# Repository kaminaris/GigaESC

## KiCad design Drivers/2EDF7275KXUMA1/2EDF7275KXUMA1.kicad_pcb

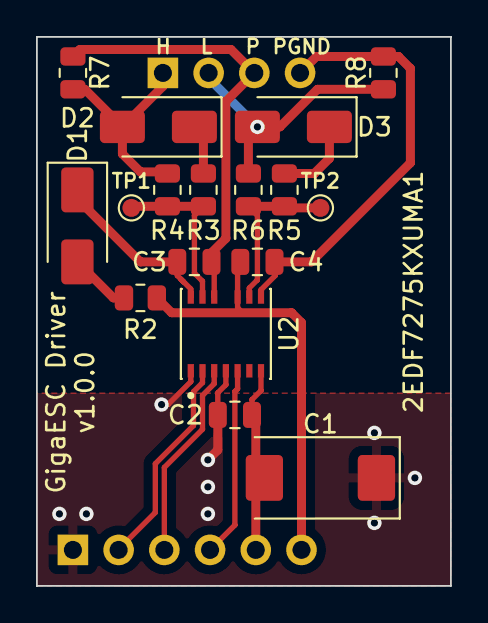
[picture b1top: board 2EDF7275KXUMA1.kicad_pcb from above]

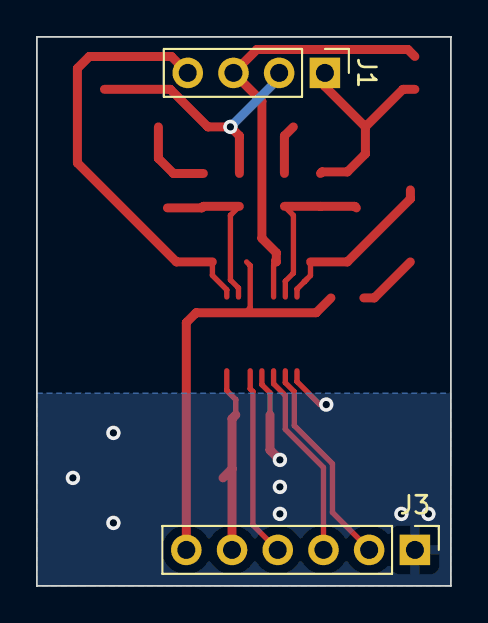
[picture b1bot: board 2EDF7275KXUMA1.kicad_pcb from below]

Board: 2 copper layers, 23.0 x 30.5 mm, 19 parts (2 on the bottom side), 16 nets.

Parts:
C1: 47u 25v Tant; CP_EIA-7343-31_Kemet-D
C2: 100n; C_0805_2012Metric
C3, C4: 4.7u 25v; C_0805_2012Metric
D1, D2, D3: SS520F; D_SMA
J1: Output; PinHeader_1x04_P2.54mm_Vertical
J3: Input; PinHeader_1x06_P2.54mm_Vertical
R2, R3, R4, R5, R6: 2.2; R_0805_2012Metric
R7, R8: 4.7k; R_0805_2012Metric
TP1, TP2: TestPoint; TestPoint_Pad_D1.0mm
U2: 2EDF7275KXUMA1; IC_2EDF7275KXUMA2

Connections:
+3.3V: C1.2, C2.1, J3.5, U2.7 (VDDI)
+15V: C4.1, J3.6, R2.1, U2.10 (VDDB)
/DISABLE: J3.4, U2.5 (DISABLE)
/H: J3.2, U2.2 (INA)
/L: J3.3, U2.3 (INB)
/PH: D2.2 (A), J1.1, R4.2, R7.2
/PHASE: C3.2, J1.3, R7.1, U2.11 (GNDA)
/PHASE_GROUND: C4.2, J1.4, R8.1, U2.8 (GNDB)
/PL: D3.2 (A), J1.2, R6.2, R8.2
GND: C1.1, C2.2, J3.1, U2.1 (GNDI), U2.4 (SLDON)
unnamed: D1.2 (A), R2.2
unnamed: C3.1, D1.1 (K), U2.13 (VDDA)
unnamed: D2.1 (K), R3.2
unnamed: D3.1 (K), R5.2
unnamed: R3.1, R4.1, TP1.1, U2.12 (OUTA)
unnamed: R5.1, R6.1, TP2.1, U2.9 (OUTB)

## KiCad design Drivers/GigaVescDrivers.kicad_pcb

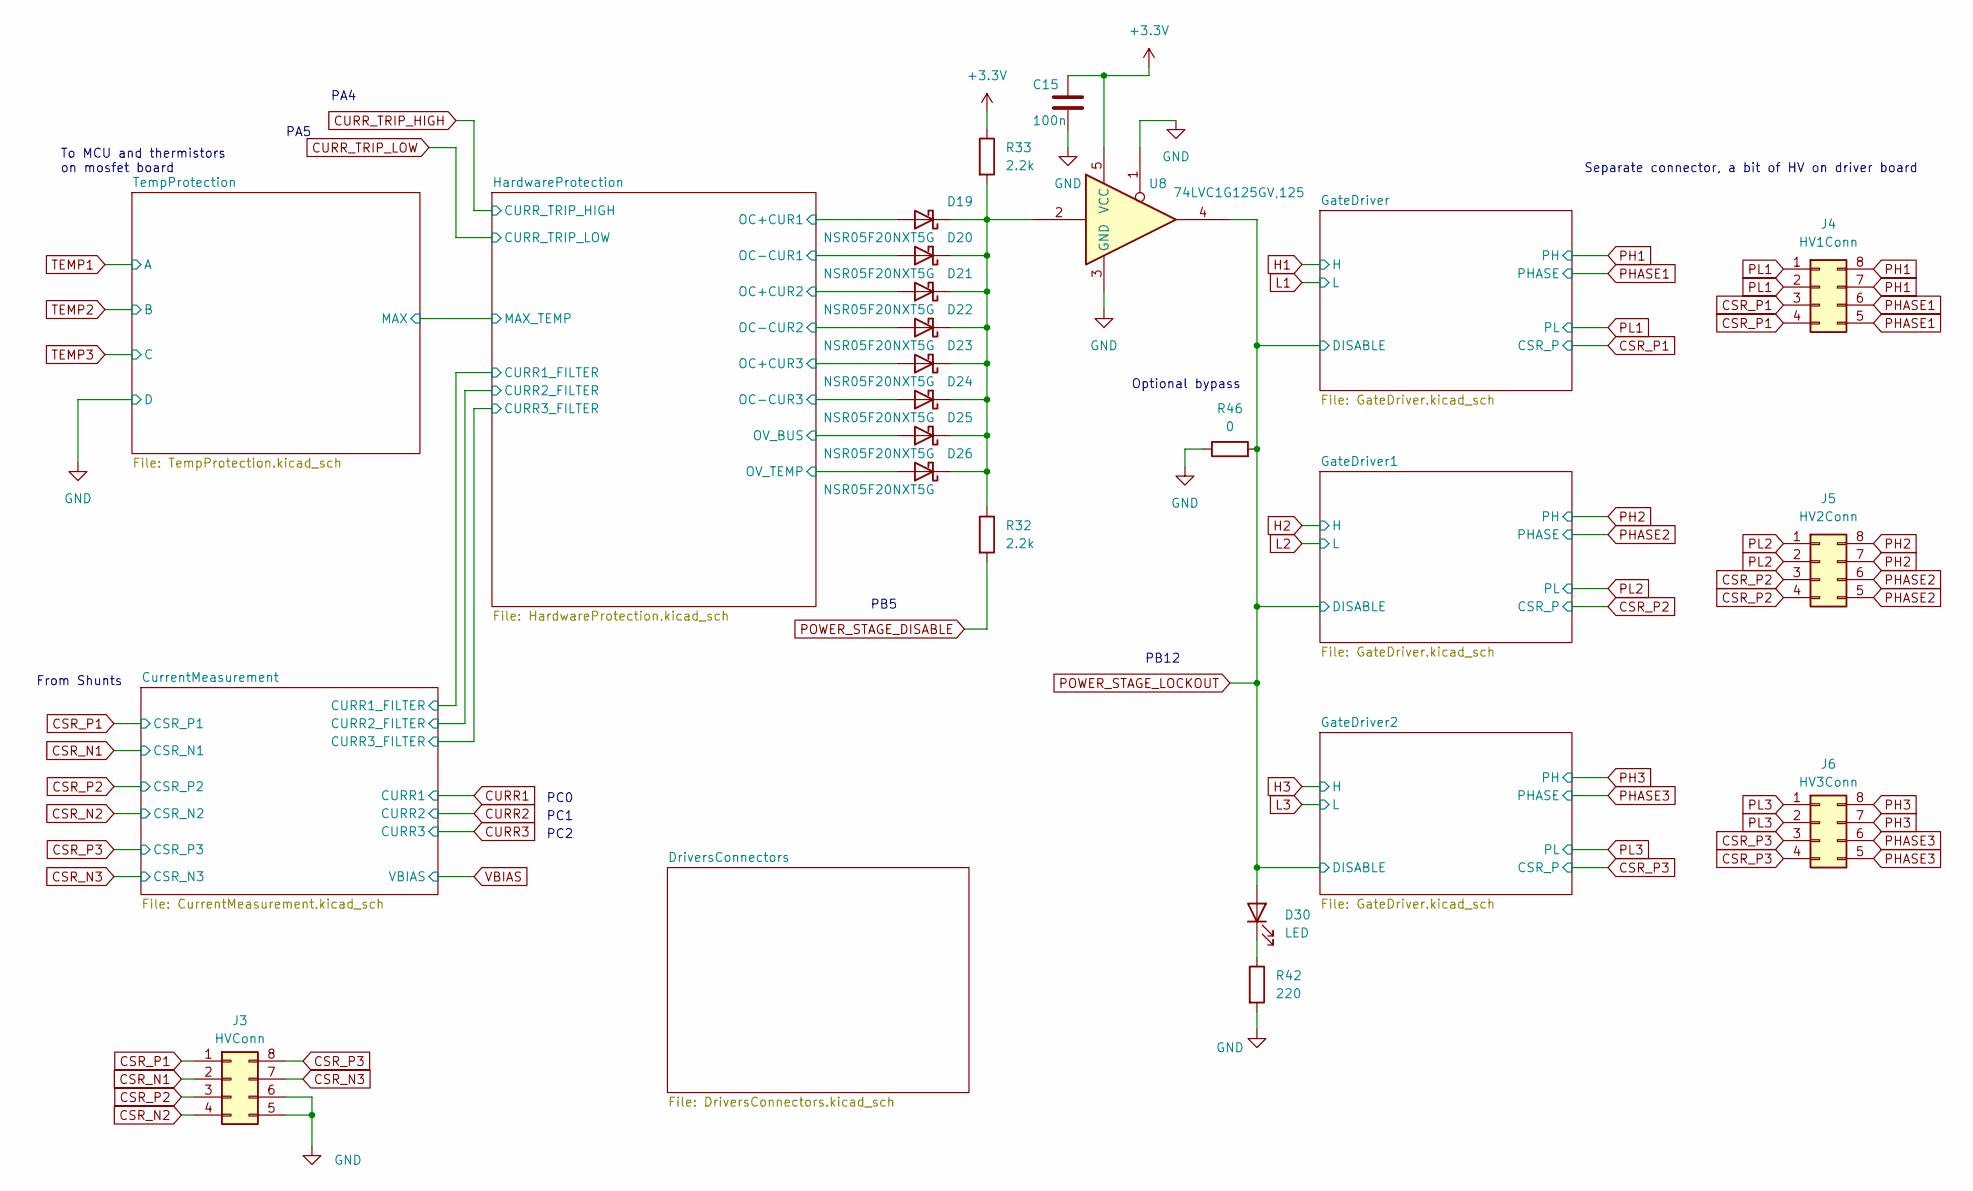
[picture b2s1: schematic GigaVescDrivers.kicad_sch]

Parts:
C15: 100n; C_0805_2012Metric
D19, D20, D21, D22, D23, D24, D25, D26: NSR05F20NXT5G; D_0402_1005Metric
D30: LED; LED_0805_2012Metric
J3: HVConn; PinHeader_2x04_P2.54mm_Vertical
J4: HV1Conn; PinHeader_2x04_P2.54mm_Vertical
J5: HV2Conn; PinHeader_2x04_P2.54mm_Vertical
J6: HV3Conn; PinHeader_2x04_P2.54mm_Vertical
R32, R33: 2.2k; R_0805_2012Metric
R42: 220; R_0805_2012Metric
R46: 0; R_0805_2012Metric
U8: 74LVC1G125GV,125; TSOP-5_1.65x3.05mm_P0.95mm

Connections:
+3.3V: C15.1, R33.1, U8.5 (VCC); also elsewhere on the board
/HardwareProtection/OC+CUR1: D19.2 (A); also elsewhere on the board
/HardwareProtection/OC+CUR2: D21.2 (A); also elsewhere on the board
/HardwareProtection/OC+CUR3: D23.2 (A); also elsewhere on the board
/HardwareProtection/OC-CUR1: D20.2 (A); also elsewhere on the board
/HardwareProtection/OC-CUR2: D22.2 (A); also elsewhere on the board
/HardwareProtection/OC-CUR3: D24.2 (A); also elsewhere on the board
/HardwareProtection/OV_BUS: D25.2 (A); also elsewhere on the board
/HardwareProtection/OV_TEMP: D26.2 (A); also elsewhere on the board
CSR_N1: J3.2; also elsewhere on the board
CSR_N2: J3.4; also elsewhere on the board
CSR_N3: J3.7; also elsewhere on the board
CSR_P1: J3.1, J4.3, J4.4; also elsewhere on the board
CSR_P2: J3.3, J5.3, J5.4; also elsewhere on the board
CSR_P3: J3.8, J6.3, J6.4; also elsewhere on the board
GND: C15.2, J3.5, J3.6, R42.2, R46.1, U8.1, U8.3 (GND); also elsewhere on the board
unnamed: D19.1 (K), D20.1 (K), D21.1 (K), D22.1 (K), D23.1 (K), D24.1 (K), D25.1 (K), D26.1 (K), R32.1, R33.2, U8.2
unnamed: D30.1 (K), R42.1
PH1: J4.7, J4.8; also elsewhere on the board
PH2: J5.7, J5.8; also elsewhere on the board
PH3: J6.7, J6.8; also elsewhere on the board
PHASE1: J4.5, J4.6; also elsewhere on the board
PHASE2: J5.5, J5.6; also elsewhere on the board
PHASE3: J6.5, J6.6; also elsewhere on the board
PL1: J4.1, J4.2; also elsewhere on the board
PL2: J5.1, J5.2; also elsewhere on the board
PL3: J6.1, J6.2; also elsewhere on the board
POWER_STAGE_DISABLE: R32.2; also elsewhere on the board
POWER_STAGE_LOCKOUT: D30.2 (A), R46.2, U8.4; also elsewhere on the board

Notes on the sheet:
PA5
PA4
PC2
PB12
Optional bypass
PB5
Separate connector, a bit of HV on driver board
To MCU and thermistors on mosfet board
PC1
PC0
From Shunts

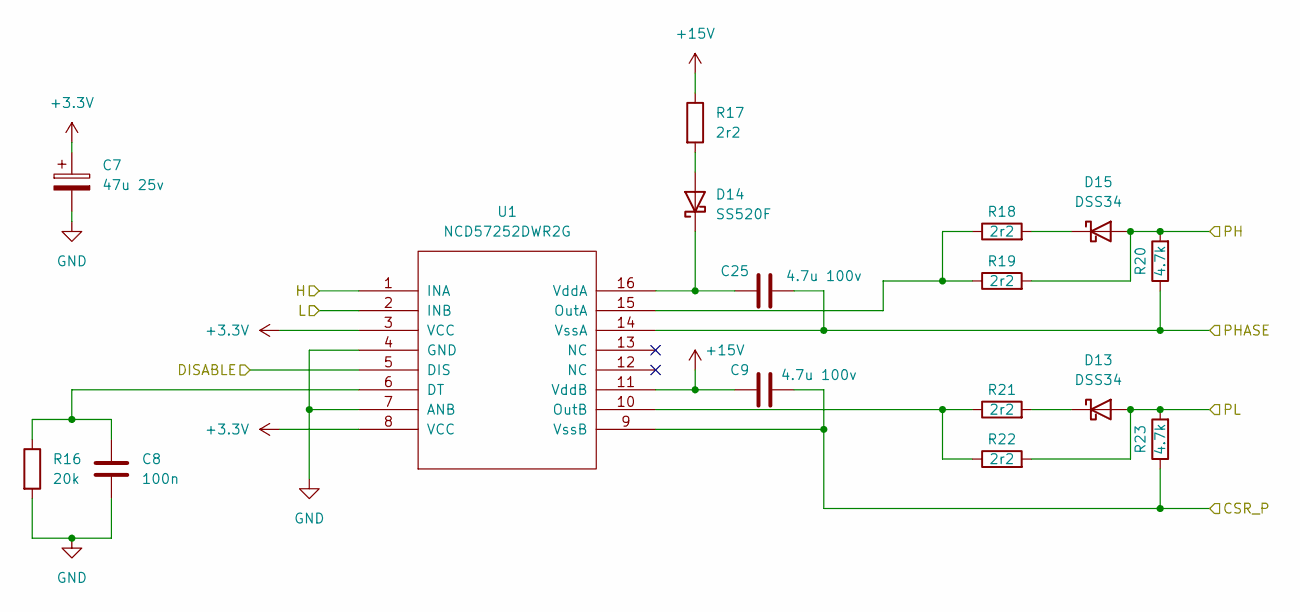
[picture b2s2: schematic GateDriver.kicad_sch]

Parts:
C7: 47u 25v; CP_Elec_5x5.4
C8: 100n; C_0805_2012Metric
C9, C25: 4.7u 100v; C_0805_2012Metric
D13, D15: DSS34; D_SOD-123F
D14: SS520F; D_SMA
R16: 20k; R_0805_2012Metric
R17, R18, R19, R21, R22: 2r2; R_0805_2012Metric
R20, R23: 4.7k; R_0805_2012Metric
U1: NCD57252DWR2G; SOIC-16W_7.5x10.3mm_P1.27mm

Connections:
+3.3V: C7.1, U1.3 (VCC), U1.8 (VCC); also elsewhere on the board
+15V: C9.1, R17.1, U1.11 (VddB); also elsewhere on the board
CSR_P1: C9.2, R23.1, U1.9 (VssB); also elsewhere on the board
GND: C7.2, C8.2, R16.2, U1.4 (GND), U1.7 (ANB); also elsewhere on the board
H1: U1.1 (INA); also elsewhere on the board
L1: U1.2 (INB); also elsewhere on the board
unnamed: D13.1 (K), R21.2
unnamed: D14.2 (A), R17.2
unnamed: C25.1, D14.1 (K), U1.16 (VddA)
unnamed: D15.1 (K), R18.2
unnamed: C8.1, R16.1, U1.6 (DT)
unnamed: R18.1, R19.1, U1.15 (OutA)
unnamed: R21.1, R22.1, U1.10 (OutB)
PH1: D15.2 (A), R19.2, R20.2; also elsewhere on the board
PHASE1: C25.2, R20.1, U1.14 (VssA); also elsewhere on the board
PL1: D13.2 (A), R22.2, R23.2; also elsewhere on the board
POWER_STAGE_LOCKOUT: U1.5 (DIS); also elsewhere on the board

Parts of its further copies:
C10, C13, C26, C27: 4.7u 100v; C_0805_2012Metric
C11, C16: 47u 25v; CP_Elec_5x5.4
C12, C17: 100n; C_0805_2012Metric
D16, D27: SS520F; D_SMA
D17, D18, D28, D29: DSS34; D_SOD-123F
R24, R34: 20k; R_0805_2012Metric
R25, R26, R27, R28, R29, R35, R36, R37, R38, R39: 2r2; R_0805_2012Metric
R30, R31, R40, R41: 4.7k; R_0805_2012Metric
U7, U9: NCD57252DWR2G; SOIC-16W_7.5x10.3mm_P1.27mm

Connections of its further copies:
+3.3V: C11.1, C16.1, U7.3 (VCC), U7.8 (VCC), U9.3 (VCC), U9.8 (VCC); also elsewhere on the board
+15V: C10.1, C13.1, R25.1, R35.1, U7.11 (VddB), U9.11 (VddB); also elsewhere on the board
CSR_P2: C10.2, R31.1, U7.9 (VssB); also elsewhere on the board
CSR_P3: C13.2, R41.1, U9.9 (VssB); also elsewhere on the board
GND: C11.2, C12.2, C16.2, C17.2, R24.2, R34.2, U7.4 (GND), U7.7 (ANB), U9.4 (GND), U9.7 (ANB); also elsewhere on the board
H2: U7.1 (INA); also elsewhere on the board
H3: U9.1 (INA); also elsewhere on the board
L2: U7.2 (INB); also elsewhere on the board
L3: U9.2 (INB); also elsewhere on the board
unnamed: D16.2 (A), R25.2
unnamed: C26.1, D16.1 (K), U7.16 (VddA)
unnamed: D17.1 (K), R26.2
unnamed: D18.1 (K), R28.2
unnamed: D27.2 (A), R35.2
unnamed: C27.1, D27.1 (K), U9.16 (VddA)
unnamed: D28.1 (K), R36.2
unnamed: D29.1 (K), R38.2
unnamed: C12.1, R24.1, U7.6 (DT)
unnamed: R26.1, R27.1, U7.15 (OutA)
unnamed: R28.1, R29.1, U7.10 (OutB)
unnamed: C17.1, R34.1, U9.6 (DT)
unnamed: R36.1, R37.1, U9.15 (OutA)
unnamed: R38.1, R39.1, U9.10 (OutB)
PH2: D17.2 (A), R27.2, R30.2; also elsewhere on the board
PH3: D28.2 (A), R37.2, R40.2; also elsewhere on the board
PHASE2: C26.2, R30.1, U7.14 (VssA); also elsewhere on the board
PHASE3: C27.2, R40.1, U9.14 (VssA); also elsewhere on the board
PL2: D18.2 (A), R29.2, R31.2; also elsewhere on the board
PL3: D29.2 (A), R39.2, R41.2; also elsewhere on the board
POWER_STAGE_LOCKOUT: U7.5 (DIS), U9.5 (DIS); also elsewhere on the board

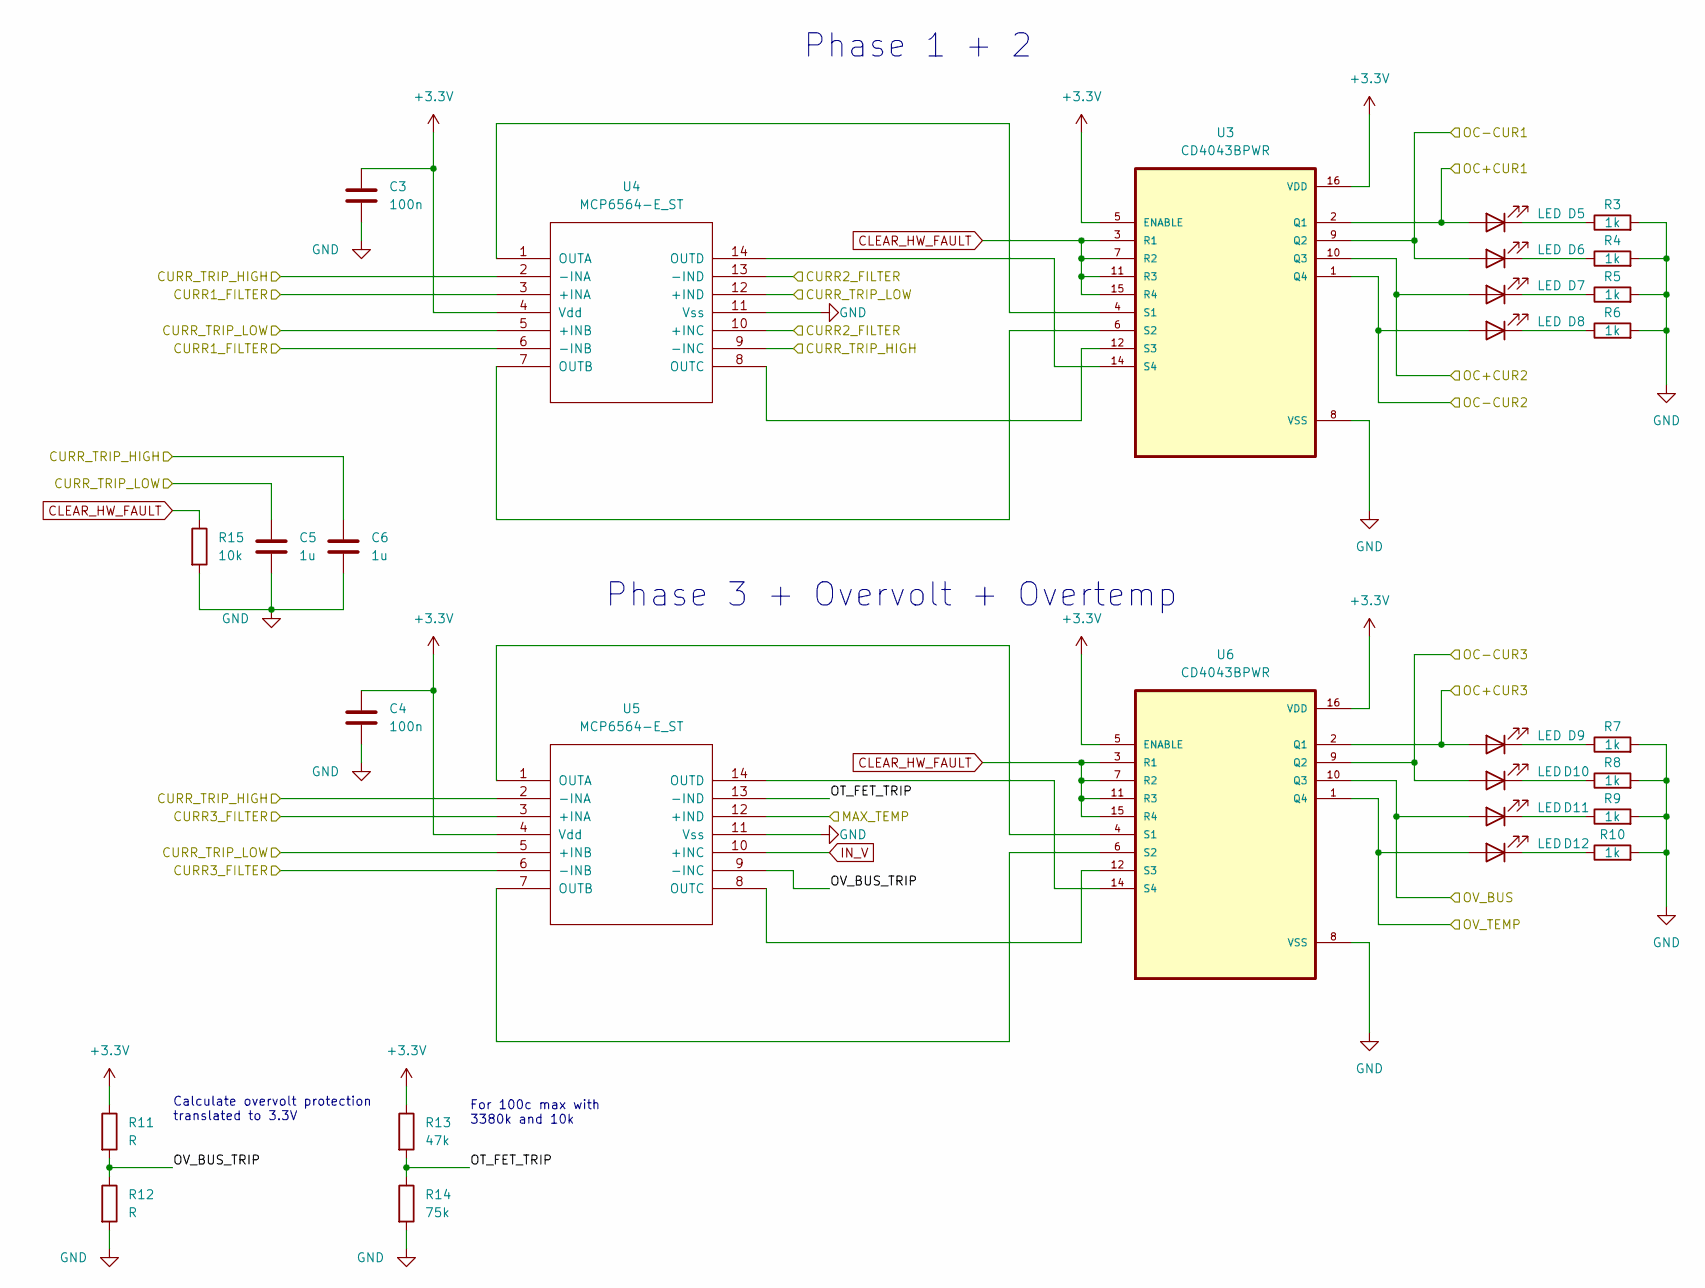
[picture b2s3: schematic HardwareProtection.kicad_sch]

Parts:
C3, C4: 100n; C_0805_2012Metric
C5, C6: 1u; C_0805_2012Metric
D5, D6, D7, D8, D9, D10, D11, D12: LED; LED_0805_2012Metric
R3, R4, R5, R6, R7, R8, R9, R10: 1k; R_0805_2012Metric
R11, R12: R; R_0805_2012Metric
R13: 47k; R_0805_2012Metric
R14: 75k; R_0805_2012Metric
R15: 10k; R_0805_2012Metric
U3, U6: CD4043BPWR; TSSOP-16_4.4x5mm_P0.65mm
U4, U5: MCP6564-E_ST; TSSOP-14_4.4x5mm_P0.65mm

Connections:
+3.3V: C3.1, C4.1, R11.1, R13.1, U3.5 (ENABLE), U3.16 (VDD), U4.4 (Vdd), U5.4 (Vdd), U6.5 (ENABLE), U6.16 (VDD); also elsewhere on the board
/CurrentMeasurement/CURR1_FILTER: U4.3 (+INA), U4.6 (-INB); also elsewhere on the board
/CurrentMeasurement/CURR2_FILTER: U4.10 (+INC), U4.13 (-IND); also elsewhere on the board
/CurrentMeasurement/CURR3_FILTER: U5.3 (+INA), U5.6 (-INB); also elsewhere on the board
/HardwareProtection/MAX_TEMP: U5.12 (+IND); also elsewhere on the board
/HardwareProtection/OC+CUR1: D5.2 (A), U3.2 (Q1); also elsewhere on the board
/HardwareProtection/OC+CUR2: D7.2 (A), U3.10 (Q3); also elsewhere on the board
/HardwareProtection/OC+CUR3: D9.2 (A), U6.2 (Q1); also elsewhere on the board
/HardwareProtection/OC-CUR1: D6.2 (A), U3.9 (Q2); also elsewhere on the board
/HardwareProtection/OC-CUR2: D8.2 (A), U3.1 (Q4); also elsewhere on the board
/HardwareProtection/OC-CUR3: D10.2 (A), U6.9 (Q2); also elsewhere on the board
/HardwareProtection/OT_FET_TRIP: R13.2, R14.1, U5.13 (-IND)
/HardwareProtection/OV_BUS: D11.2 (A), U6.10 (Q3); also elsewhere on the board
/HardwareProtection/OV_BUS_TRIP: R11.2, R12.1, U5.9 (-INC)
/HardwareProtection/OV_TEMP: D12.2 (A), U6.1 (Q4); also elsewhere on the board
CLEAR_HW_FAULT: R15.1, U3.3 (R1), U3.7 (R2), U3.11 (R3), U3.15 (R4), U6.3 (R1), U6.7 (R2), U6.11 (R3), U6.15 (R4); also elsewhere on the board
CURR_TRIP_HIGH: C6.1, U4.2 (-INA), U4.9 (-INC), U5.2 (-INA); also elsewhere on the board
CURR_TRIP_LOW: C5.1, U4.5 (+INB), U4.12 (+IND), U5.5 (+INB); also elsewhere on the board
GND: C3.2, C4.2, C5.2, C6.2, R3.2, R4.2, R5.2, R6.2, R7.2, R8.2, R9.2, R10.2, R12.2, R14.2, R15.2, U3.8 (VSS), U4.11 (Vss), U5.11 (Vss), U6.8 (VSS); also elsewhere on the board
IN_V: U5.10 (+INC); also elsewhere on the board
unnamed: D5.1 (K), R3.1
unnamed: D6.1 (K), R4.1
unnamed: D7.1 (K), R5.1
unnamed: D8.1 (K), R6.1
unnamed: D9.1 (K), R7.1
unnamed: D10.1 (K), R8.1
unnamed: D11.1 (K), R9.1
unnamed: D12.1 (K), R10.1
unnamed: U3.4 (S1), U4.1 (OUTA)
unnamed: U3.6 (S2), U4.7 (OUTB)
unnamed: U3.12 (S3), U4.8 (OUTC)
unnamed: U3.14 (S4), U4.14 (OUTD)
unnamed: U5.1 (OUTA), U6.4 (S1)
unnamed: U5.7 (OUTB), U6.6 (S2)
unnamed: U5.8 (OUTC), U6.12 (S3)
unnamed: U5.14 (OUTD), U6.14 (S4)

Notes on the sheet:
For 100c max with 3380k and 10k
Phase 1 + 2
Phase 3 + Overvolt + Overtemp
Calculate overvolt protection translated to 3.3V

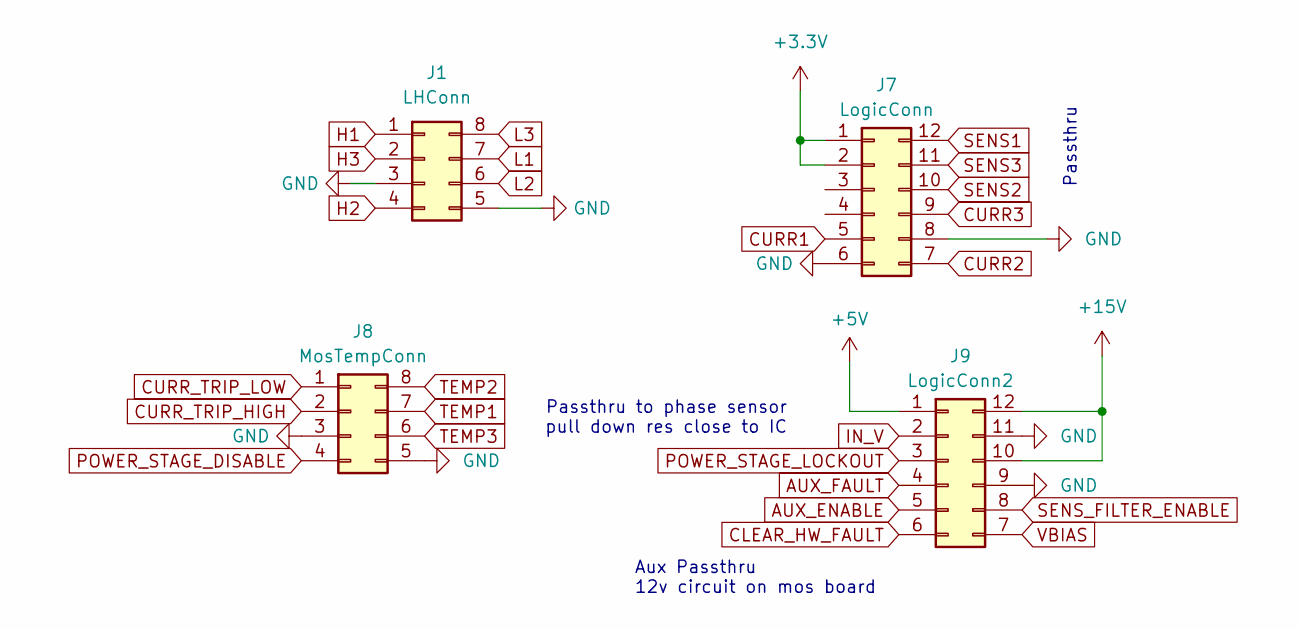
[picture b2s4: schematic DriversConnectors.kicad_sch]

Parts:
J1: LHConn; PinSocket_2x04_P2.54mm_Vertical
J7: LogicConn; PinSocket_2x06_P2.54mm_Vertical
J8: MosTempConn; PinSocket_2x04_P2.54mm_Vertical
J9: LogicConn2; PinSocket_2x06_P2.54mm_Vertical

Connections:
+3.3V: J7.1, J7.2; also elsewhere on the board
+5V: J9.1; also elsewhere on the board
+15V: J9.10, J9.12; also elsewhere on the board
AUX_ENABLE: J9.5
AUX_FAULT: J9.4
CLEAR_HW_FAULT: J9.6; also elsewhere on the board
CURR1: J7.5; also elsewhere on the board
CURR2: J7.7; also elsewhere on the board
CURR3: J7.9; also elsewhere on the board
CURR_TRIP_HIGH: J8.2; also elsewhere on the board
CURR_TRIP_LOW: J8.1; also elsewhere on the board
GND: J1.3, J1.5, J7.6, J7.8, J8.3, J8.5, J9.9, J9.11; also elsewhere on the board
H1: J1.1; also elsewhere on the board
H2: J1.4; also elsewhere on the board
H3: J1.2; also elsewhere on the board
IN_V: J9.2; also elsewhere on the board
L1: J1.7; also elsewhere on the board
L2: J1.6; also elsewhere on the board
L3: J1.8; also elsewhere on the board
POWER_STAGE_DISABLE: J8.4; also elsewhere on the board
POWER_STAGE_LOCKOUT: J9.3; also elsewhere on the board
SENS1: J7.12
SENS2: J7.10
SENS3: J7.11
SENS_FILTER_ENABLE: J9.8
TEMP1: J8.7; also elsewhere on the board
TEMP2: J8.8; also elsewhere on the board
TEMP3: J8.6; also elsewhere on the board
VBIAS: J9.7; also elsewhere on the board

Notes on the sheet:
Passthru
Aux Passthru 12v circuit on mos board
Passthru to phase sensor pull down res close to IC

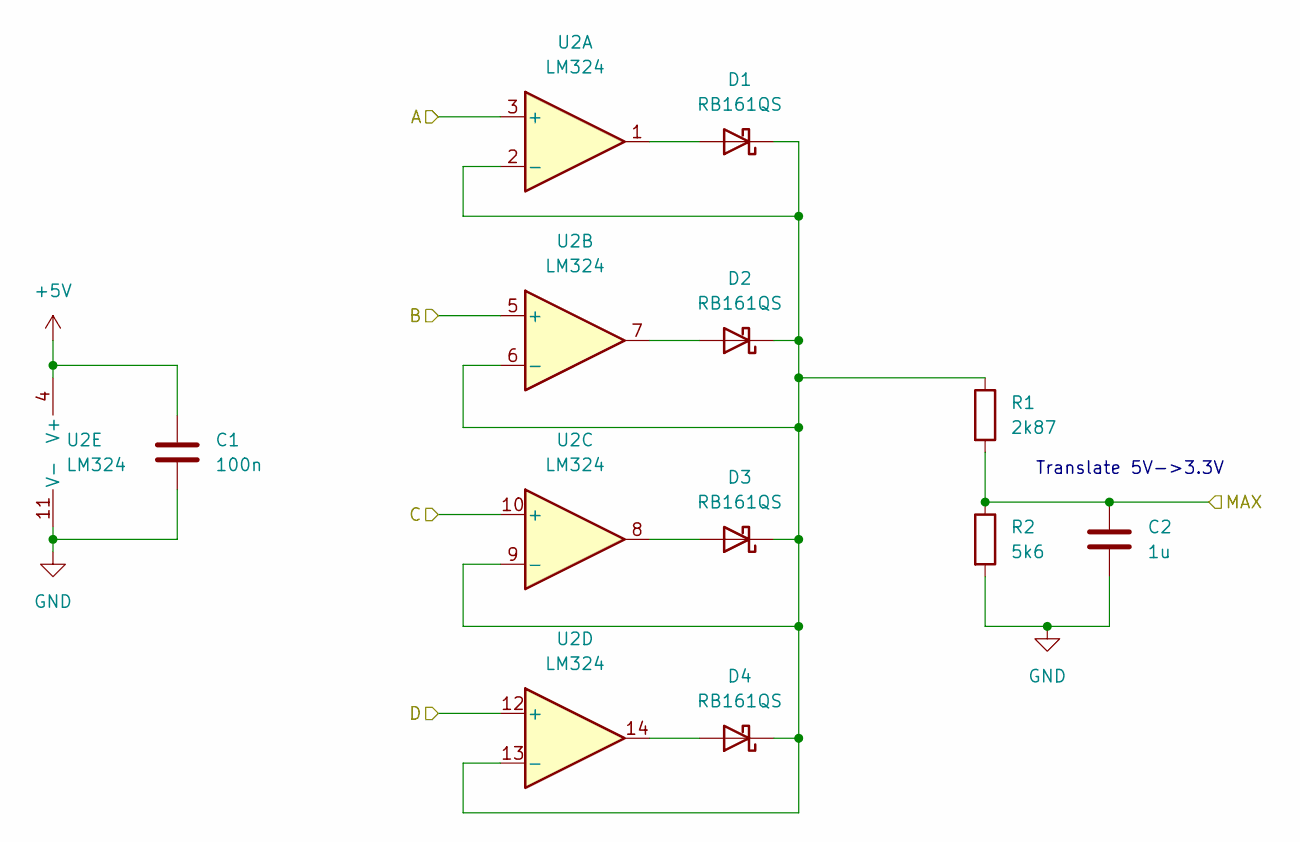
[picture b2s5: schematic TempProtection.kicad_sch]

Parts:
C1: 100n; C_0805_2012Metric
C2: 1u; C_0805_2012Metric
D1, D2, D3, D4: RB161QS; SOD882D
R1: 2k87; R_0805_2012Metric
R2: 5k6; R_0805_2012Metric
U2: LM324; TSSOP-14_4.4x5mm_P0.65mm

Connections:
+5V: C1.1, U2.4 (V+); also elsewhere on the board
/HardwareProtection/MAX_TEMP: C2.1, R1.2, R2.1; also elsewhere on the board
GND: C1.2, C2.2, R2.2, U2.11 (V-), U2.12 (+); also elsewhere on the board
unnamed: D1.2 (A), U2.1
unnamed: D1.1 (K), D2.1 (K), D3.1 (K), D4.1 (K), R1.1, U2.2 (-), U2.6 (-), U2.9 (-), U2.13 (-)
unnamed: D2.2 (A), U2.7
unnamed: D3.2 (A), U2.8
unnamed: D4.2 (A), U2.14
TEMP1: U2.3 (+); also elsewhere on the board
TEMP2: U2.5 (+); also elsewhere on the board
TEMP3: U2.10 (+); also elsewhere on the board

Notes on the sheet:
Translate 5V->3.3V

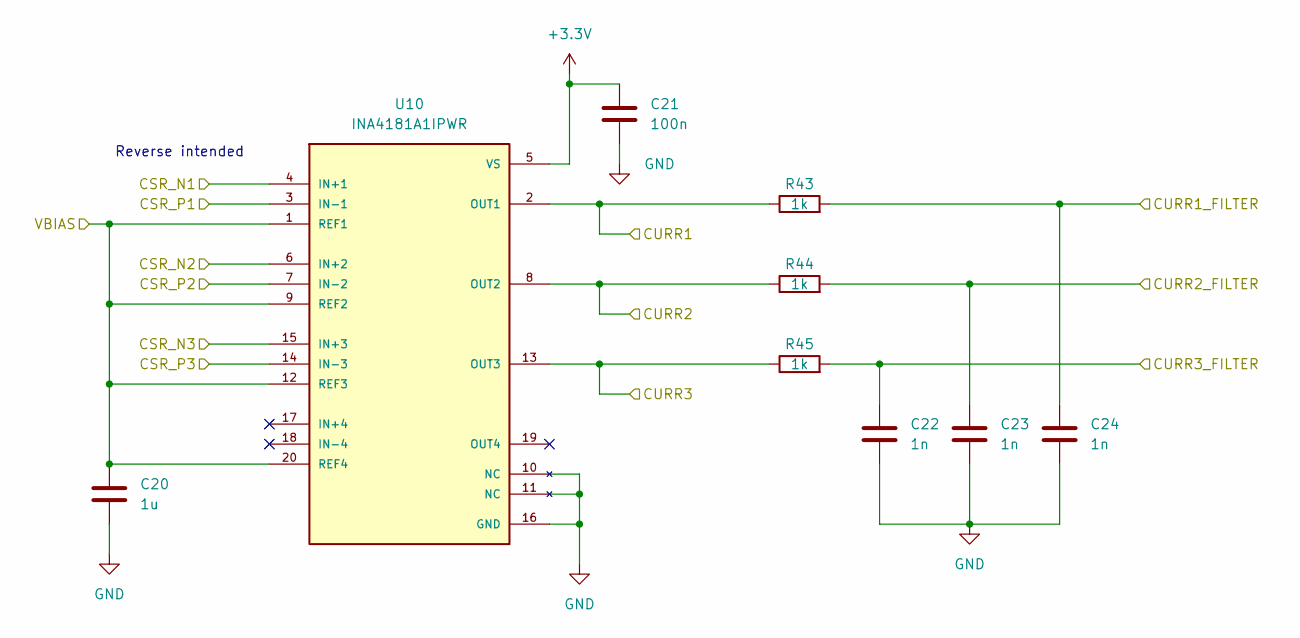
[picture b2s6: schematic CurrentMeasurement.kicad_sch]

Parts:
C20: 1u; C_0805_2012Metric
C21: 100n; C_0805_2012Metric
C22, C23, C24: 1n; C_0805_2012Metric
R43, R44, R45: 1k; R_0805_2012Metric
U10: INA4181A1IPWR; TSSOP-20_4.4x6.5mm_P0.65mm; PARTREV May 2020

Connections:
+3.3V: C21.1, U10.5 (VS); also elsewhere on the board
/CurrentMeasurement/CURR1_FILTER: C24.1, R43.2; also elsewhere on the board
/CurrentMeasurement/CURR2_FILTER: C23.1, R44.2; also elsewhere on the board
/CurrentMeasurement/CURR3_FILTER: C22.1, R45.2; also elsewhere on the board
CSR_N1: U10.4 (IN+1); also elsewhere on the board
CSR_N2: U10.6 (IN+2); also elsewhere on the board
CSR_N3: U10.15 (IN+3); also elsewhere on the board
CSR_P1: U10.3 (IN-1); also elsewhere on the board
CSR_P2: U10.7 (IN-2); also elsewhere on the board
CSR_P3: U10.14 (IN-3); also elsewhere on the board
CURR1: R43.1, U10.2 (OUT1); also elsewhere on the board
CURR2: R44.1, U10.8 (OUT2); also elsewhere on the board
CURR3: R45.1, U10.13 (OUT3); also elsewhere on the board
GND: C20.2, C21.2, C22.2, C23.2, C24.2, U10.10 (NC), U10.11 (NC), U10.16 (GND); also elsewhere on the board
VBIAS: C20.1, U10.1 (REF1), U10.9 (REF2), U10.12 (REF3), U10.20 (REF4); also elsewhere on the board

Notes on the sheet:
Reverse intended

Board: 2 copper layers, 118 parts (4 on the bottom side), 96 nets, no tracks yet.

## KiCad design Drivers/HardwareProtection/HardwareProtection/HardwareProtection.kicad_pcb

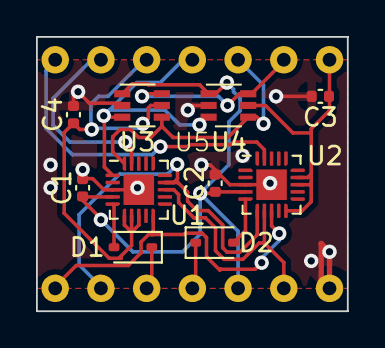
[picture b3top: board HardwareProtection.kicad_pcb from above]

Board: 2 copper layers, 17.3 x 15.2 mm, 11 parts (0 on the bottom side), 16 nets.

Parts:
C1, C2, C3, C4: 1u; C_0402_1005Metric
D1, D2: 1N5819WS; D_SOD-323
U1, U2: ATTINY1616-MNR; VQFN-20-1EP_3x3mm_P0.4mm_EP1.7x1.7mm
U3: TPL0401A-10DCKR; Texas_R-PDSO-G6
U4: TPL0401B-10DCKR; Texas_R-PDSO-G6
U5: HWProt

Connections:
+3.3V: C1.1, C2.1, U1.4 (VCC), U2.4 (VCC), U3.1 (VDD), U4.1 (VDD), U5.12 (+3.3V)
+3.3VADC: U3.6 (H), U4.6 (H), U5.6 (CURR_TRIP_LOW)
CURR1: U1.13 (PB1), U2.7 (PA6), U5.13 (+3.3VADC)
CURR2: U1.10 (PB4), U2.8 (PA7), U5.8 (CURR2)
CURR3: U1.14 (PB0), U2.6 (PA5), U5.9 (CURR3)
CURR_TRIP_HIGH: C4.1, U1.6 (PA5), U1.7 (PA6), U1.8 (PA7), U3.5 (W), U5.3 (SCL)
CURR_TRIP_LOW: C3.1, U2.10 (PB4), U2.13 (PB1), U2.14 (PB0), U4.5 (W), U5.7 (CURR1)
DISABLE: D2.1 (K), U5.11 (HW_OVERCURRENT)
GND: C1.2, C2.2, C3.2, C4.2, U1.3 (GND), U1.21 (GND), U2.3 (GND), U2.21 (GND), U3.2 (GND), U4.2 (GND), U5.14 (GND)
HW_OVERCURRENT: D1.1 (K), U5.10 (DISABLE)
unnamed: D1.2 (A), U1.5 (PA4)
unnamed: D2.2 (A), U2.5 (PA4)
SCL: U1.1 (PA2), U3.3 (SCL), U4.3 (SCL), U5.4 (SDA)
SDA: U1.20 (PA1), U3.4 (SDA), U4.4 (SDA), U5.5 (CURR_TRIP_HIGH)
UPDI: U1.19 (~RESET/PA0), U5.2 (UPDI2)
UPDI2: U2.19 (~RESET/PA0), U5.1 (UPDI)

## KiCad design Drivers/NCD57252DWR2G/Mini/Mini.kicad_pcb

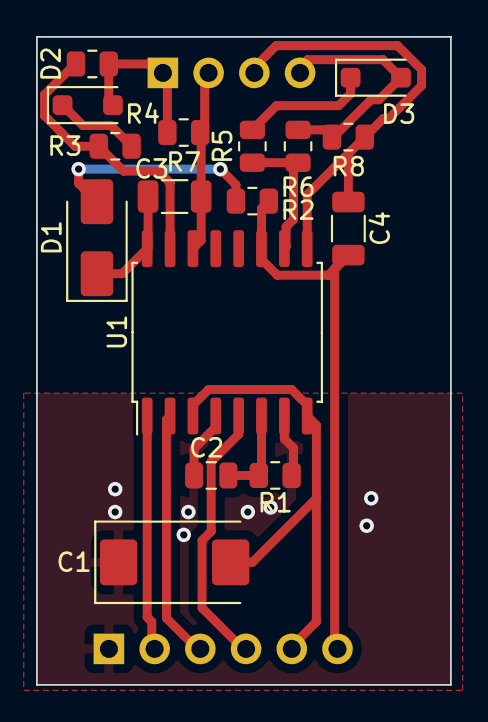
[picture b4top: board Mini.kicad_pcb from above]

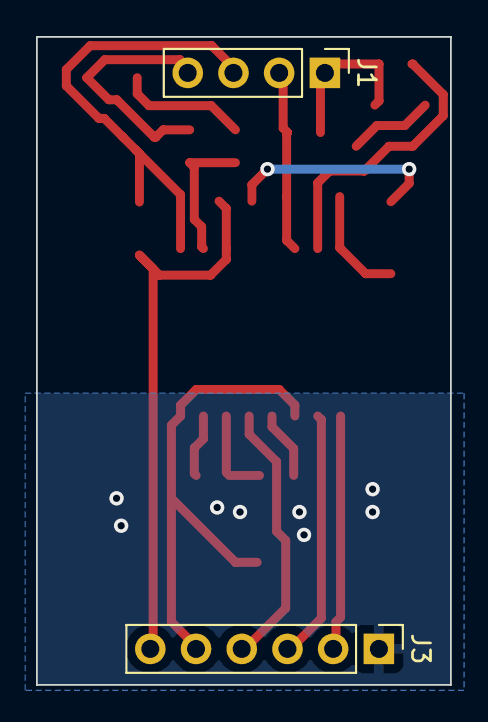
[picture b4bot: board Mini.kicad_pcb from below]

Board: 2 copper layers, 23.0 x 36.0 mm, 18 parts (2 on the bottom side), 17 nets.

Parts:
C1: 47u 25v Tant; CP_EIA-7343-31_Kemet-D
C2: 100n; C_0805_2012Metric
C3, C4: 4.7u 50v; C_1206_3216Metric
D1: SS520F; D_SMA
D2, D3: DSS34; D_SOD-123F
J1: Output; PinHeader_1x04_P2.54mm_Vertical
J3: Input; PinHeader_1x06_P2.54mm_Vertical
R1: 20k; R_0805_2012Metric
R2, R3, R4, R5, R6: 2r2; R_0805_2012Metric
R7, R8: 4.7k; R_0805_2012Metric
U1: NCD57252DWR2G; SOIC-16W_7.5x10.3mm_P1.27mm

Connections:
+3.3V: C1.2, J3.5, U1.3 (VCC), U1.8 (VCC)
+15V: C4.1, J3.6, R2.1, U1.11 (VddB)
/CSR_P: C4.2, J1.3, R8.1, U1.9 (VssB)
/DISABLE: J3.4, U1.5 (DIS)
/H: J3.2, U1.1 (INA)
/L: J3.3, U1.2 (INB)
/PH: D2.2 (A), J1.1, R4.2, R7.2
/PHASE: C3.2, J1.2, R7.1, U1.14 (VssA)
/PL: D3.2 (A), J1.4, R6.2, R8.2
GND: C1.1, C2.2, J3.1, R1.2, U1.4 (GND), U1.7 (ANB)
unnamed: D1.2 (A), R2.2
unnamed: C3.1, D1.1 (K), U1.16 (VddA)
unnamed: D2.1 (K), R3.2
unnamed: D3.1 (K), R5.2
unnamed: C2.1, R1.1, U1.6 (DT)
unnamed: R3.1, R4.1, U1.15 (OutA)
unnamed: R5.1, R6.1, U1.10 (OutB)
